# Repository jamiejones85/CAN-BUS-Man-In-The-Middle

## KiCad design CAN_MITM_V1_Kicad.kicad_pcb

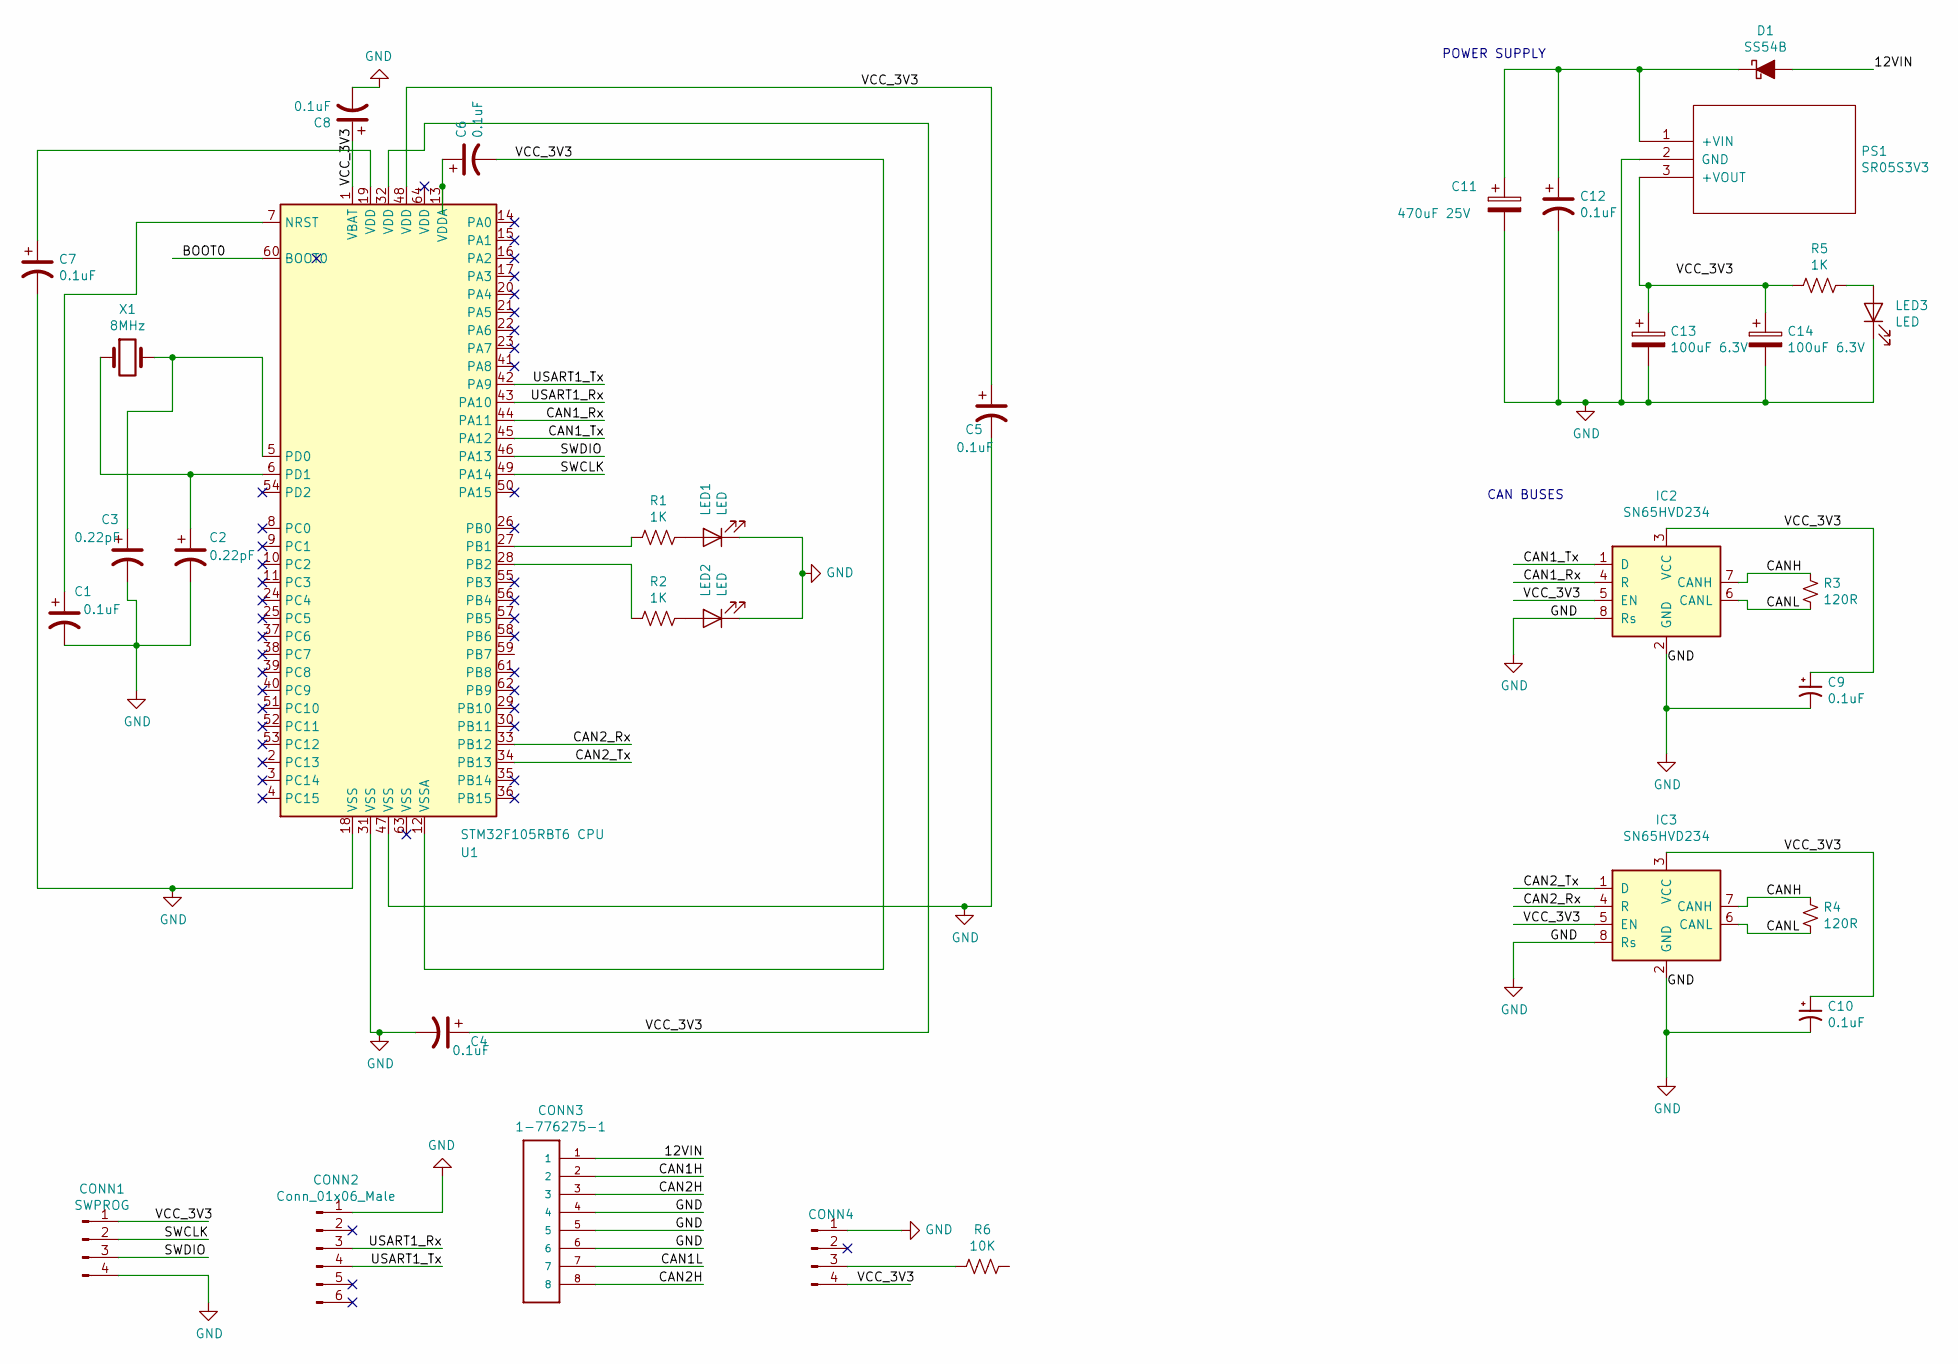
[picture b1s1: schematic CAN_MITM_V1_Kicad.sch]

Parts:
C1, C4, C5, C6, C7, C8, C9, C10, C12: 0.1uF; C_0805_2012Metric
C2, C3: 0.22pF; C_0805_2012Metric
C11: 470uF 25V; CP_Elec_10x10
C13, C14: 100uF 6.3V; C_0805_2012Metric
CONN1: SWPROG; TerminalBlock_TE_282834-4_1x04_P2.54mm_Horizontal
CONN2: Conn_01x06_Male; TerminalBlock_TE_282834-6_1x06_P2.54mm_Horizontal
CONN3: 1-776275-1; TE_1-776275-1
CONN4: Conn_01x04_Male; TerminalBlock_TE_282834-4_1x04_P2.54mm_Horizontal
D1: SS54B; D_SMA
IC2, IC3: SN65HVD234; SOIC-8_3.9x4.9mm_P1.27mm
LED1, LED2, LED3: LED; LED_0805_2012Metric
PS1: SR05S3V3
R1, R2, R5: 1K; R_0805_2012Metric
R3, R4: 120R; R_0805_2012Metric
R6: 10K; R_0805_2012Metric
U1: STM32F105RBT6 CPU; LQFP-64_10x10mm_P0.5mm
X1: 8MHz; Crystal_SMD_5032-2Pin_5.0x3.2mm

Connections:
/12VIN: CONN3.1, D1.2 (A)
/BOOT0: U1.60 (BOOT0)
/CAN1H: CONN3.2
/CAN1L: CONN3.7
/CAN1_Rx: IC2.4 (R), U1.44 (PA11)
/CAN1_Tx: IC2.1 (D), U1.45 (PA12)
/CAN2H: CONN3.3, CONN3.8
/CAN2_Rx: IC3.4 (R), U1.33 (PB12)
/CAN2_Tx: IC3.1 (D), U1.34 (PB13)
/CANH: IC2.7 (CANH), IC3.7 (CANH), R3.1, R4.1
/CANL: IC2.6 (CANL), IC3.6 (CANL), R3.2, R4.2
/SWCLK: CONN1.2, U1.49 (PA14)
/SWDIO: CONN1.3, U1.46 (PA13)
/USART1_Rx: CONN2.3, U1.43 (PA10)
/USART1_Tx: CONN2.4, U1.42 (PA9)
/VCC_3V3: C4.1, C5.1, C6.2, C8.1, C9.1, C10.1, CONN1.1, CONN4.4, IC2.3 (VCC), IC2.5 (EN), IC3.3 (VCC), IC3.5 (EN), U1.1 (VBAT), U1.12 (VSSA), U1.32 (VDD), U1.48 (VDD)
GND: C1.2, C2.2, C3.2, C4.2, C5.2, C7.2, C8.2, C9.2, C10.2, C11.2, C12.2, C13.2, C14.2, CONN1.4, CONN2.1, CONN3.4, CONN3.5, CONN3.6, CONN4.1, IC2.2 (GND), IC2.8 (Rs), IC3.2 (GND), IC3.8 (Rs), LED1.1 (K), LED2.1 (K), LED3.1 (K), PS1.2 (GND), U1.18 (VSS), U1.31 (VSS), U1.47 (VSS)
unnamed: C1.1, U1.7 (NRST)
unnamed: C2.1, U1.6 (PD1), X1.1
unnamed: C3.1, U1.5 (PD0), X1.2
unnamed: C6.1, U1.13 (VDDA)
unnamed: C7.1, U1.19 (VDD)
unnamed: C11.1, C12.1, D1.1 (K), PS1.1 (+VIN)
unnamed: C13.1, C14.1, PS1.3 (+VOUT), R5.2
unnamed: CONN4.3, R6.2
unnamed: LED1.2 (A), R1.1
unnamed: LED2.2 (A), R2.1
unnamed: LED3.2 (A), R5.1
unnamed: R1.2, U1.27 (PB1)
unnamed: R2.2, U1.28 (PB2)

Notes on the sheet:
CAN BUSES
POWER SUPPLY

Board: 2 copper layers, 33 parts (0 on the bottom side), 27 nets, no tracks yet.

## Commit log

2020-03-02 Starting on translating to Kicad
2020-03-02 Adding more to the Kicad schematic
2020-03-03 Adding Schematic
2020-03-03 Fixing wrong footprint on C11
2020-03-05 Routed PCB and updated some of the schematic
